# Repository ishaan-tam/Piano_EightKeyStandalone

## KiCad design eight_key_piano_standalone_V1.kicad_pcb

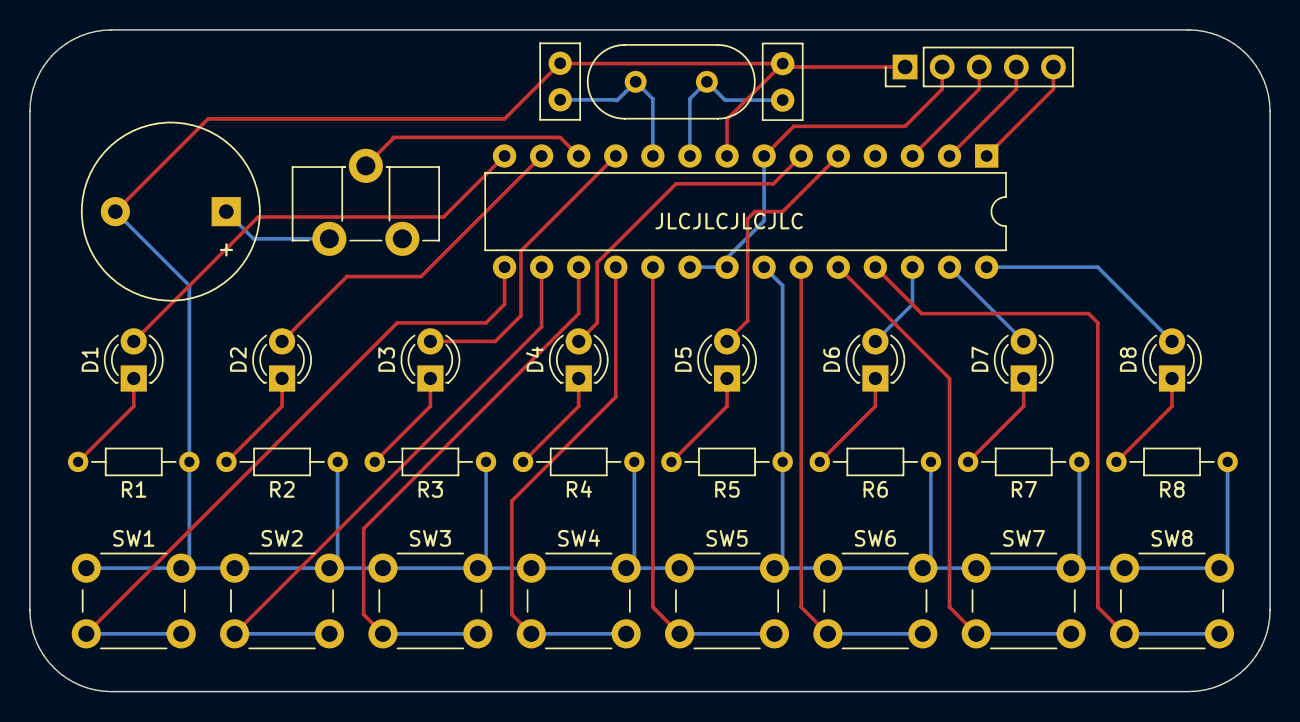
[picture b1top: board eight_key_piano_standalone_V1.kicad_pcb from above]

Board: 2 copper layers, 84.9 x 45.3 mm, 31 parts (0 on the bottom side), 33 nets.

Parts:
BZ1: Buzzer; Buzzer_12x9.5RM7.6
C1, C2: 22pf; C_Disc_D5.0mm_W2.5mm_P2.50mm
D1, D2, D3, D4, D5, D6, D7, D8: LED; LED_D3.0mm
J1: Conn_01x05_Pin; PinHeader_1x05_P2.54mm_Vertical
R1, R2, R3, R4, R5, R6, R7, R8: 220 Ohm; R_Axial_DIN0204_L3.6mm_D1.6mm_P7.62mm_Horizontal
RV1: R_Potentiometer; Potentiometer_ACP_CA9-H5_Horizontal
SW1, SW2, SW3, SW4, SW5, SW6, SW7, SW8: SW_Push; SW_PUSH_6mm
U1: ATmega328-P; DIP-28_W7.62mm
Y1: 16MHz; Crystal_HC49-4H_Vertical

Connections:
+5V: J1.2, U1.7 (VCC), U1.20 (AVCC), U1.21 (AREF)
/BUZZER: RV1.2, U1.12 (PD6)
/LED1: D1.2 (A), U1.14 (PB0)
/LED2: D2.2 (A), U1.13 (PD7)
/LED3: D3.2 (A), U1.11 (PD5)
/LED4: D4.2 (A), U1.6 (PD4)
/LED5: D5.2 (A), U1.5 (PD3)
/LED6: D6.2 (A), U1.26 (PC3)
/LED7: D7.2 (A), U1.27 (PC4)
/LED8: D8.2 (A), U1.28 (PC5)
/RESET: J1.5, U1.1 (~RESET/PC6)
/RX: J1.4, U1.2 (PD0)
/SW1: SW1.2, U1.15 (PB1)
/SW2: SW2.2, U1.16 (PB2)
/SW3: SW3.2, U1.17 (PB3)
/SW4: SW4.2, U1.18 (PB4)
/SW5: SW5.2, U1.19 (PB5)
/SW6: SW6.2, U1.23 (PC0)
/SW7: SW7.2, U1.24 (PC1)
/SW8: SW8.2, U1.25 (PC2)
/TX: J1.3, U1.3 (PD1)
GND: BZ1.2 (+), C1.2, C2.2, J1.1, R1.1, R2.1, R3.1, R4.1, R5.1, R6.1, R7.1, R8.1, SW1.1, SW2.1, SW3.1, SW4.1, SW5.1, SW6.1, SW7.1, SW8.1, U1.8 (GND), U1.22 (GND)
unnamed: BZ1.1 (-), RV1.1
unnamed: D1.1 (K), R1.2
unnamed: D2.1 (K), R2.2
unnamed: D3.1 (K), R3.2
unnamed: D4.1 (K), R4.2
unnamed: D5.1 (K), R5.2
unnamed: D6.1 (K), R6.2
unnamed: D7.1 (K), R7.2
unnamed: D8.1 (K), R8.2
unnamed: C2.1, U1.9 (XTAL1/PB6), Y1.2
unnamed: C1.1, U1.10 (XTAL2/PB7), Y1.1
